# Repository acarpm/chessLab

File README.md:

# ChessLab — Documentation technique

Échiquier connecté détectant la position des pièces (capteurs à effet Hall) et affichant un retour visuel case par case (LEDs RGB adressables), pour visualiser une partie et aider à l'apprentissage du jeu.

## Architecture système

```
                        ESP32-C6
        WiFi 6 · BLE 5 · RISC-V 160 MHz · 512 KB SRAM
                            |
        +-------------------+-------------------+
        |                   |                   |
  Capteurs Hall         LEDs RGB           Alimentation
   (8x8 = 64)          (8x8 = 64)          Pack 18650
```

## Hardware

### Capteurs de position — SS49E

Capteur à effet Hall Analogique, suffisant pour détecter la présence ou l'absence d'une pièce sur une case. 

### LEDs — WS2812B (NeoPixel)

64 LEDs adressables individuellement, câblées en une seule chaîne série (une ligne de données, montage serpentin case par case). Alimentation 5 V, consommation crête d'environ 60 mA par LED.

### Multiplexage des capteurs Hall

64 capteurs analogiques dépassent le nombre de broches disponibles sur l'ESP32-C6. Solution retenue : multiplexeurs analogiques 74HC4051 (8 voies vers 1), soit 8 multiplexeurs pour 64 capteurs, ramenant le besoin à environ 11 broches ESP32.

### Alimentation — 18650

- 2 cellules 18650 montées en parallèle (~6000 mAh)
- Gestion de charge : IC TP4056
- Régulation :
  - 5 V / 3 A pour les LEDs WS2812B (convertisseur buck MP3608)
  - 3,3 V pour l'ESP32 et les capteurs Hall (LDO AMS1117-3.3)

## Circuit d'alimentation (mise sous tension)

Commutation assurée par un MOSFET P-Channel AO3401, piloté par le bouton d'alimentation et maintenu par l'ESP32 :

```
VBAT
 |
 R1 10k
 |
 +----------------------> Gate AO3401 (P-MOS)
 |                              |
 |        +---- R2 100k --------+
 |        |
 |     Source AO3401 = VBAT
 |        |
 |       Drain --------------------> VSYS
 |                                     |
BTN_PWR                          (MT3608 + AMS1117)
 |                                     |
 +---- vers Gate                 ESP32-C6
                                   |         |
                          GPIO_PWR_HOLD  GPIO_BTN_PWR
                          (maintien ON)  (lecture bouton)
```

**Séquence d'allumage**
1. Appui sur BTN_PWR
2. La gate du MOSFET passe à GND, le MOSFET conduit
3. VSYS s'active, l'ESP32 démarre
4. L'ESP32 maintient son GPIO à l'état bas pour garder le MOSFET conducteur
5. Le bouton peut être relâché, le système reste alimenté

**Extinction logicielle**
1. Inactivité détectée (par exemple 10 minutes sans coup joué)
2. Sauvegarde de l'état de la partie si nécessaire
3. Le GPIO passe à l'état haut, le MOSFET se bloque et coupe l'alimentation

**Extinction manuelle**
1. Appui long sur BTN_PWR (environ 3 secondes)
2. Détection par l'ESP32 via le GPIO de lecture du bouton
3. Même séquence que l'extinction logicielle

## Répartition des composants entre les deux cartes

| Carte principale | Carte d'alimentation |
|---|---|
| ESP32-C6 | TP4056 |
| Connecteur USB-C | DW01A + FS8205A |
| 64× WS2812B | Connecteur 18650 |
| 64× SS49E | MT3608 (5 V) |
| 8× 74HC4051 | AMS1117 (3,3 V) |
| 1× 74HC138 | Commutation MOSFET |
| BTN_BOOT + BTN_RESET | BTN_PWR + LED power |
| Connecteur JST vers carte d'alimentation | Connecteur JST vers carte principale |

Les deux cartes sont reliées par un connecteur JST 4 broches :

| Broche | Signal |
|---|---|
| 1 | VBAT (18650+) |
| 2 | GND |
| 3 | 5 V (sortie MT3608 vers carte principale) |
| 4 | 3,3 V (sortie AMS1117 vers carte principale) |

## Layout PCB

- Routage serpentin des WS2812B (entrée/sortie de données case par case)
- Matrices de capteurs Hall organisées en lignes/colonnes vers les multiplexeurs
- Épaisseur de PCB standard : 1,6 mm
- Couche diffusante imprimée en 3D au-dessus des LEDs

### Largeurs de piste

| Signal | Largeur |
|---|---|
| Données / GPIO | 0,25 mm |
| Alimentation 3,3 V | 0,5 mm |
| Alimentation 5 V (LEDs) | 1,0 mm |
| VBAT | 1,0 mm |
| VSYS | 1,0 mm |
| USB D+ / D- | 0,2 mm |

### Vias

| Type | Perçage | Pad |
|---|---|---|
| Standard | 0,4 mm | 0,8 mm |
| Puissance | 0,6 mm | 1,2 mm |

## Pinout ESP32-C6

| Broche | GPIO | Fonction |
|---|---|---|
| 13 | GPIO12 | USB D- |
| 14 | GPIO13 | USB D+ |
| 8 | GPIO0 | Mux — sélection canal S0 |
| 9 | GPIO1 | Mux — sélection canal S1 |
| 27 | GPIO2 | Mux — sélection canal S2 |
| 16 | GPIO18 | 74HC138 — sélection rangée A0 |
| 25 | GPIO16 | 74HC138 — sélection rangée A1 |
| 24 | GPIO17 | 74HC138 — sélection rangée A2 |
| 26 | GPIO3 | Lecture capteurs Hall (A_OUT) |
| 17 | GPIO19 | Données WS2812B (via résistance 33 Ω) |
| 18 | GPIO20 | VBAT |
| 15 | GPIO9 | Bouton BOOT |
| 19 | GPIO21 | Lecture bouton d'alimentation (BTN_PWR) |
| 20 | GPIO22 | Maintien alimentation (PWR_HOLD) |

## Fixation des pièces

Aimants cylindriques N52, Ø6×3 mm, insérés dans la base de chaque pièce et collés à l'époxy dans un logement imprimé en 3D. Ce choix permet une détection fiable par les capteurs Hall tout en restant invisible une fois la pièce posée.

## Boîtier

Hauteur totale estimée : 25 à 30 mm, dimensionnée pour loger la carte principale, la carte d'alimentation et les deux packs 18650.

## Firmware

Architecture logicielle sous FreeRTOS, organisée en tâches indépendantes :

| Tâche | Rôle |
|---|---|
| Hall Scanner | Scrutation des 64 capteurs (polling 50 ms) |
| LED Controller | Traduction de l'état de l'échiquier en animation LED |
| Chess Engine | Validation des positions et des coups légaux |
| BLE/WiFi | Communication avec l'application mobile ou l'interface web |
| Battery Monitor | Suivi de la tension batterie via diviseur de tension sur ADC |

**Bibliothèques envisagées**
- `FastLED` ou `Adafruit NeoPixel` pour le pilotage des WS2812B
- `Stockfish` (version allégée, via WASM) pour le moteur d'échecs
- Interface web servie depuis la mémoire flash (SPIFFS/LittleFS)

## Feuille de route

| Phase | Objectif |
|---|---|
| P1 | Prototype d'une case (1 LED + 1 capteur Hall + multiplexeur) sur breadboard |
| P2 | PCB de test 4×4 (KiCad) pour valider le multiplexage |
| P3 | PCB complet 8×8 et boîtier v1 |
| P4 | Firmware — moteur d'échecs et application |
| P5 | Impression 3D du boîtier final et des pièces modifiées |

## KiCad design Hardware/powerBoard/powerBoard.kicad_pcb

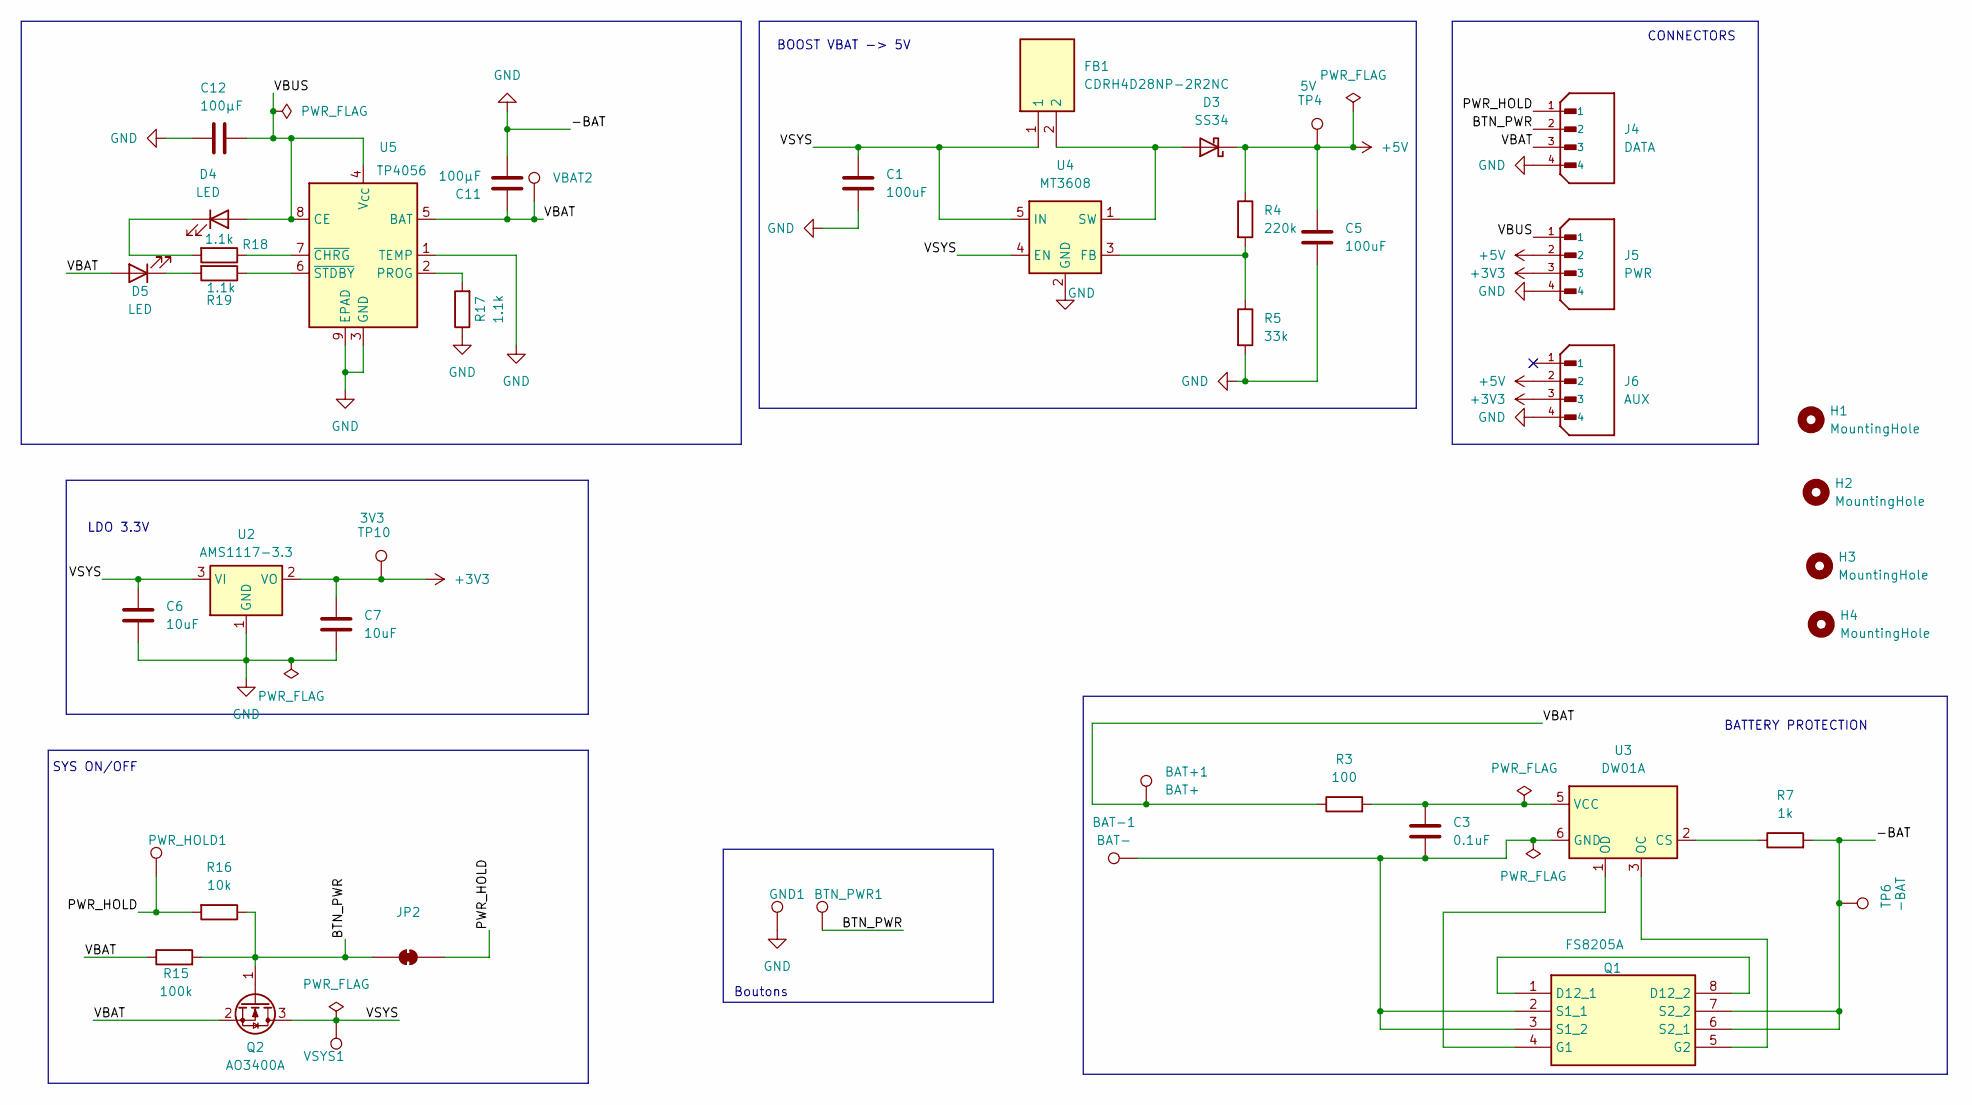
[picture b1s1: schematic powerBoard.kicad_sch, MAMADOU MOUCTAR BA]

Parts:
BAT+1: BAT+; TestPoint_Pad_4.0x4.0mm
BAT-1: BAT-; TestPoint_Pad_4.0x4.0mm
BTN_PWR1: TestPoint_Pad_4.0x4.0mm
C1, C5: 100uF; C_1206_3216Metric_Pad1.33x1.80mm_HandSolder
C3: 0.1uF; C_0603_1608Metric_Pad1.08x0.95mm_HandSolder
C6, C7: 10uF; C_0603_1608Metric_Pad1.08x0.95mm_HandSolder
C11, C12: 100µF; C_0603_1608Metric_Pad1.08x0.95mm_HandSolder
D3: SS34; D_SMA
D4, D5: LED; LED_0201_0603Metric
FB1: CDRH4D28NP-2R2NC; CDRH4D28NP100NC; Mouser Part Number 851-CDRH4D28NP-2R2NC
GND1: TestPoint_Pad_4.0x4.0mm
H1, H2, H3, H4: MountingHole; MountingHole_2.7mm_M2.5
J4: DATA; JST_B4B-XH-A_LF__SN_; PARTREV 7/4/21
J5: PWR; JST_B4B-XH-A_LF__SN_; PARTREV 7/4/21
J6: AUX; JST_B4B-XH-A_LF__SN_; PARTREV 7/4/21
JP2: SolderJumper_2_Bridged; SolderJumper-2_P1.3mm_Bridged2Bar_RoundedPad1.0x1.5mm
PWR_HOLD1: TestPoint_Pad_4.0x4.0mm
Q1: FS8205A; SOP65P640X120-8N; Manufacturer_Part_Number FS8205A
Q2: AO3400A; SOT-23
R3: 100; R_0603_1608Metric_Pad0.98x0.95mm_HandSolder
R4: 220k; R_0603_1608Metric_Pad0.98x0.95mm_HandSolder
R5: 33k; R_0603_1608Metric_Pad0.98x0.95mm_HandSolder
R7: 1k; R_0603_1608Metric_Pad0.98x0.95mm_HandSolder
R15: 100k; R_0603_1608Metric_Pad0.98x0.95mm_HandSolder
R16: 10k; R_0603_1608Metric_Pad0.98x0.95mm_HandSolder
R17, R18, R19: 1.1k; R_0603_1608Metric_Pad0.98x0.95mm_HandSolder
TP4: 5V; TestPoint_Pad_D2.0mm
TP6: -BAT; TestPoint_Pad_D2.0mm
TP10: 3V3; TestPoint_Pad_D2.0mm
U2: AMS1117-3.3; SOT-223-3_TabPin2
U3: DW01A; SOT-23-6
U4: MT3608; SOT-23-6
U5: TP4056; SOIC-8-1EP_3.9x4.9mm_P1.27mm_EP2.41x3.3mm_ThermalVias
VBAT2: TestPoint_Pad_4.0x4.0mm
VSYS1: TestPoint_Pad_4.0x4.0mm

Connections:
+3V3: C7.1, J5.3, J6.3, TP10.1 (1_1), U2.2 (VO)
+5V: C5.1, D3.1 (K), J5.2, J6.2, R4.1, TP4.1 (1_1)
/BTN_PWR: BTN_PWR1.1 (1_1), J4.2, JP2.1 (A), Q2.1 (G), R15.2, R16.1
/PWR_HOLD: J4.1, JP2.2 (B), PWR_HOLD1.1 (1_1), R16.2
/VBAT: BAT+1.1 (1_1), C11.1, D5.2 (A), J4.3, Q2.2 (S), R3.1, R15.1, U5.5 (BAT), VBAT2.1 (1_1)
/VBUS: C12.1, D4.2 (A), J5.1, U5.4 (V_{CC}), U5.8 (CE)
/VSYS: C1.1, C6.1, FB1.1, Q2.3 (D), U2.3 (VI), U4.4 (EN), U4.5 (IN), VSYS1.1 (1_1)
GND: C1.2, C5.2, C6.2, C7.2, C11.2, C12.2, GND1.1 (1_1), J4.4, J5.4, J6.4, Q1.6 (S2_1), Q1.7 (S2_2), R5.2, R7.2, R17.1, TP6.1 (1_1), U2.1 (GND), U4.2 (GND), U5.1 (TEMP), U5.3 (GND), U5.9 (EPAD)
unnamed: D3.2 (A), FB1.2, U4.1 (SW)
unnamed: D4.1 (K), R18.2
unnamed: D5.1 (K), R19.2
unnamed: Q1.1 (D12_1), Q1.8 (D12_2)
unnamed: Q1.4 (G1), U3.1 (OD)
unnamed: Q1.5 (G2), U3.3 (OC)
unnamed: BAT-1.1 (1_1), C3.2, Q1.2 (S1_1), Q1.3 (S1_2), U3.6 (GND)
unnamed: R7.1, U3.2 (CS)
unnamed: C3.1, R3.2, U3.5 (VCC)
unnamed: R4.2, R5.1, U4.3 (FB)
unnamed: R17.2, U5.2 (PROG)
unnamed: R18.1, U5.7 (~CHRG)
unnamed: R19.1, U5.6 (~STDBY)

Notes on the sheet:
BOOST VBAT -> 5V
CONNECTORS
BATTERY PROTECTION
LDO 3.3V
SYS ON/OFF
Boutons

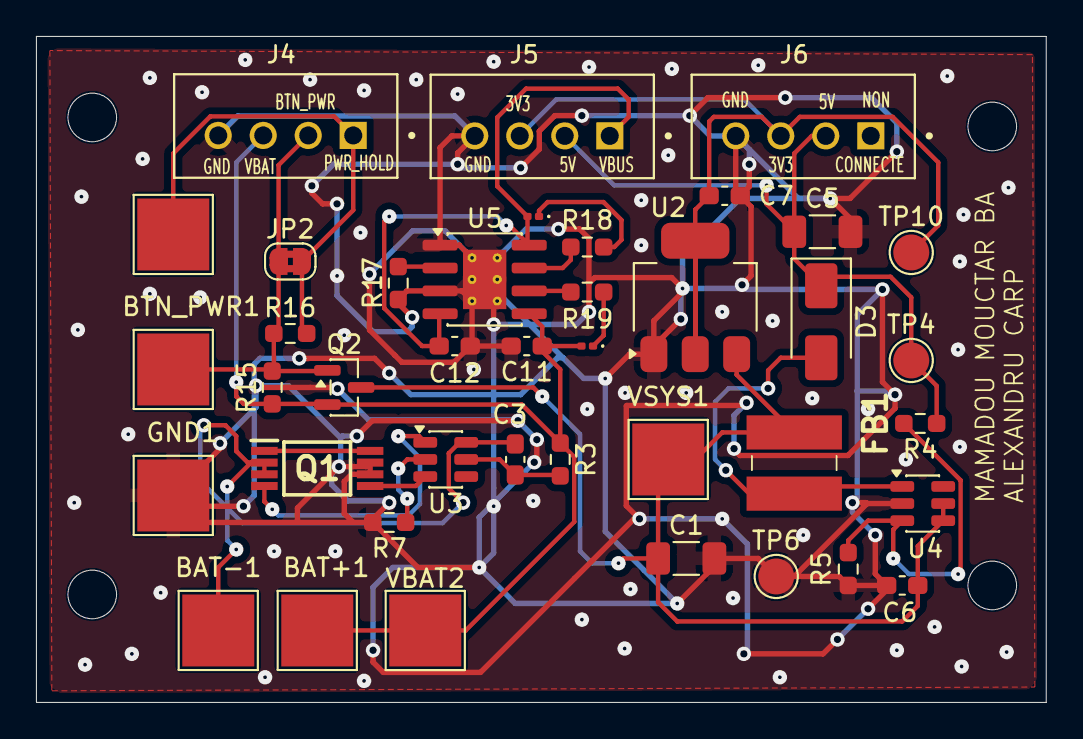
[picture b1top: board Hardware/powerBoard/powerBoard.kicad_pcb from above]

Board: 2 copper layers, 56.1 x 37.0 mm, 44 parts (0 on the bottom side), 21 nets.

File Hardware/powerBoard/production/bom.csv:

Designator,Footprint,Quantity,Value,LCSC Part #
BAT+1,TestPoint_Pad_4.0x4.0mm,1,BAT+,
BAT-1,TestPoint_Pad_4.0x4.0mm,1,BAT-,
"BTN_PWR1, GND1, PWR_HOLD1, VBAT2, VSYS1",TestPoint_Pad_4.0x4.0mm,5,~,
"C1, C5",1206,2,100uF,
"C11, C12",0603,2,100µF,
C3,0603,1,0.1uF,
"C6, C7",0603,2,10uF,
D3,D_SMA,1,SS34,
"D4, D5",0201,2,LED,
FB1,CDRH4D28NP100NC,1,CDRH4D28NP-2R2NC,
J4,JST_B4B-XH-A_LF__SN_,1,DATA,
J5,JST_B4B-XH-A_LF__SN_,1,PWR,
J6,JST_B4B-XH-A_LF__SN_,1,AUX,
Q1,SOP65P640X120-8N,1,FS8205A,
Q2,SOT-23,1,AO3400A,
R15,0603,1,100k,
R16,0603,1,10k,
"R17, R18, R19",0603,3,1.1k,
R3,0603,1,100,
R4,0603,1,220k,
R5,0603,1,33k,
R7,0603,1,1k,
TP10,TestPoint_Pad_D2.0mm,1,3V3,
TP4,TestPoint_Pad_D2.0mm,1,5V,
TP6,TestPoint_Pad_D2.0mm,1,-BAT,
U2,SOT-223-3_TabPin2,1,AMS1117-3.3,
U3,SOT-23-6,1,DW01A,
U4,SOT-23-6,1,MT3608,
U5,SOIC-8-1EP_3.9x4.9mm_P1.27mm_EP2.41x3.3mm_ThermalVias,1,TP4056,

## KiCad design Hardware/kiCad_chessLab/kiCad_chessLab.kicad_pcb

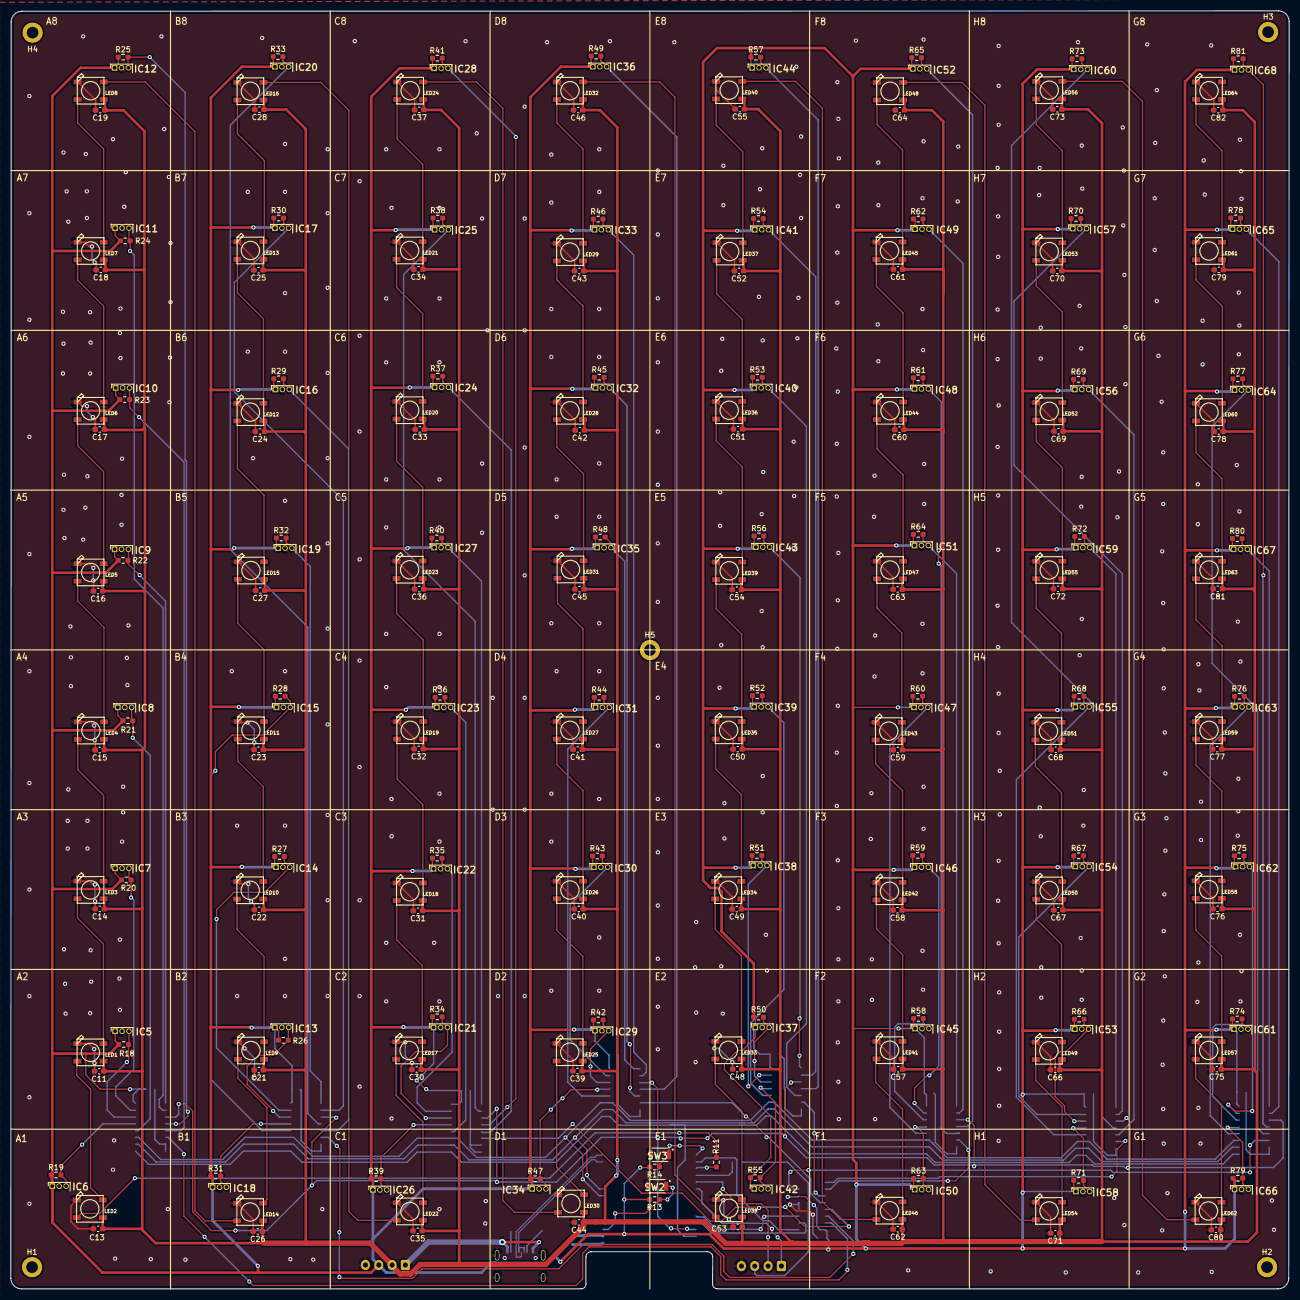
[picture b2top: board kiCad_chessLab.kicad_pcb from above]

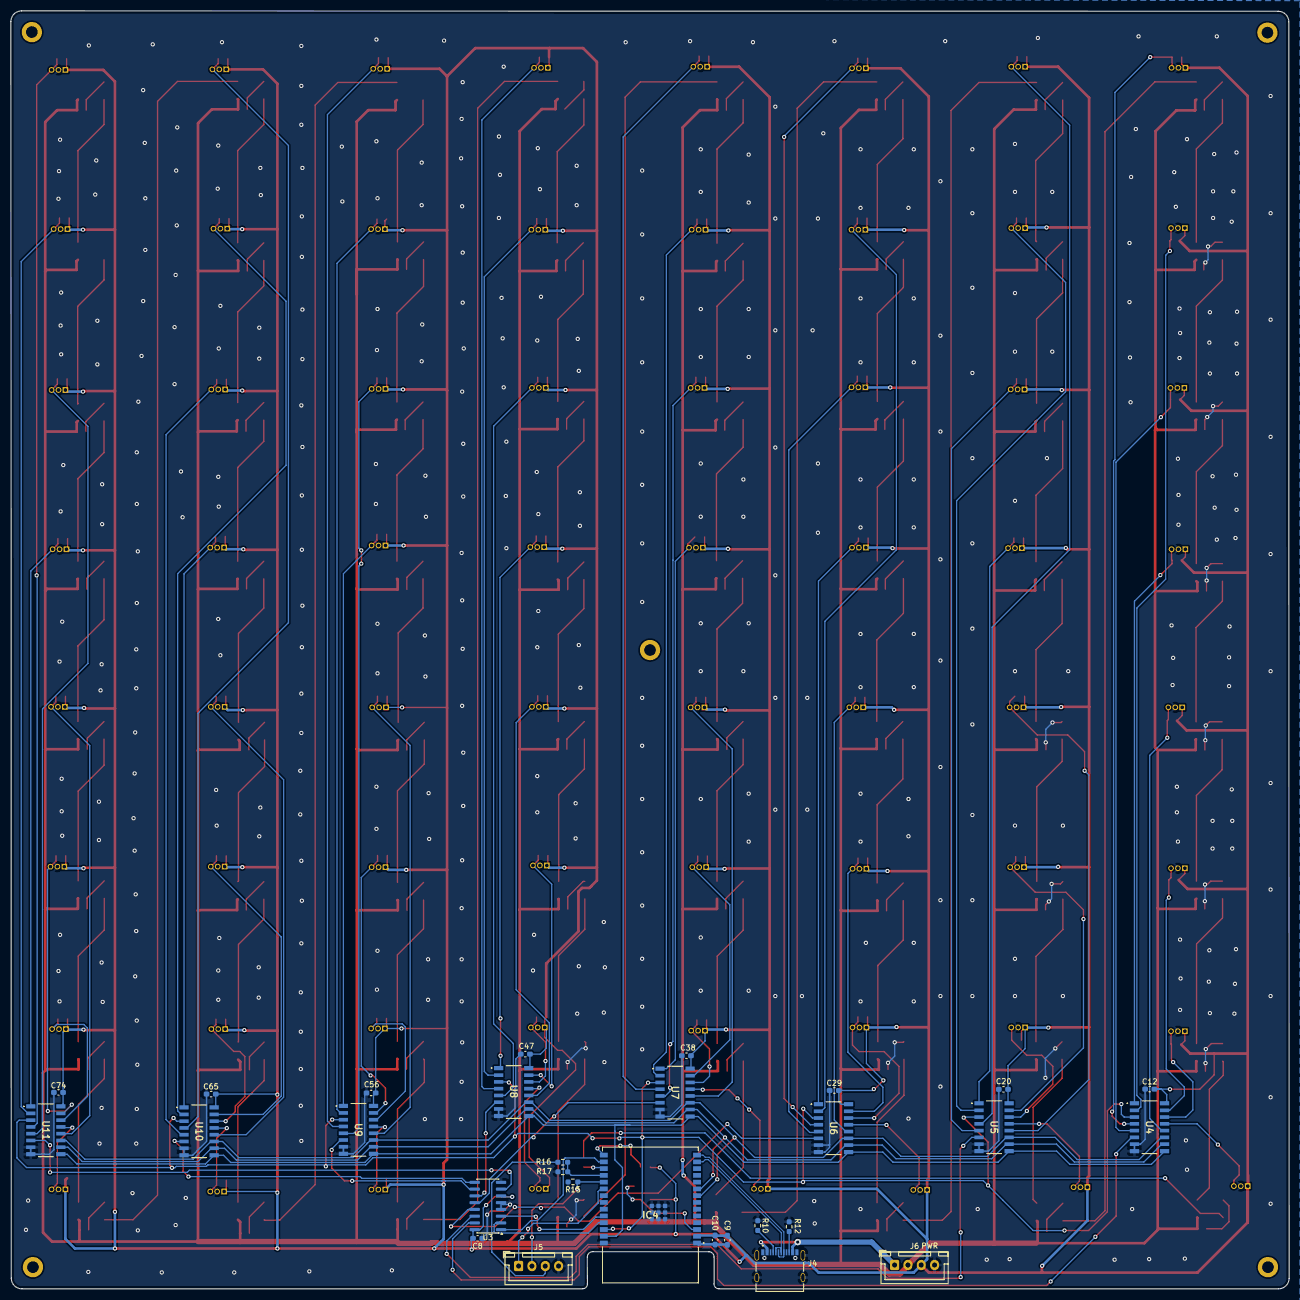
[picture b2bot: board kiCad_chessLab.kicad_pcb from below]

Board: 2 copper layers, 240.0 x 239.9 mm, 295 parts (29 on the bottom side), 158 nets.

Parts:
C8, C11, C12, C13, C14, C15, C16, C17, C18, C19, C20, C21, C22, C23, C24, C25, C26, C27, C28, C29, C30, C31, C32, C33, C34, C35, C36, C37, C38, C39, C40, C41, C42, C43, C44, C45, C46, C47, C48, C49, C50, C51, C52, C53, C54, C55, C56, C57, C58, C59, C60, C61, C62, C63, C64, C65, C66, C67, C68, C69, C70, C71, C72, C73, C74, C75, C76, C77, C78, C79, C80, C81, C82: 100nF; C_0603_1608Metric_Pad1.08x0.95mm_HandSolder
C9: 100uF; C_0603_1608Metric_Pad1.08x0.95mm_HandSolder
C10: 10uF; C_0603_1608Metric_Pad1.08x0.95mm_HandSolder
H1, H2, H3, H4, H5: MountingHole_Pad; MountingHole_2.2mm_M2_DIN965_Pad
IC4: ESP32-C6-WROOM-1-N8; ESP32C6WROOM1N8
IC5, IC6, IC7, IC8, IC9, IC10, IC11, IC12, IC13, IC14, IC15, IC16, IC17, IC18, IC19, IC20, IC21, IC22, IC23, IC24, IC25, IC26, IC27, IC28, IC29, IC30, IC31, IC32, IC33, IC34, IC35, IC36, IC37, IC38, IC39, IC40, IC41, IC42, IC43, IC44, IC45, IC46, IC47, IC48, IC49, IC50, IC51, IC52, IC53, IC54, IC55, IC56, IC57, IC58, IC59, IC60, IC61, IC62, IC63, IC64, IC65, IC66, IC67, IC68: SS49E; TO130P160X410X300-3P
J4: TYPE-C-31-M-12; HRO_TYPE-C-31-M-12
J5: DATA; JST_XH_B4B-XH-A_1x04_P2.50mm_Vertical
J6: PWR; JST_XH_B4B-XH-A_1x04_P2.50mm_Vertical
LED1, LED2, LED3, LED4, LED5, LED6, LED7, LED8, LED9, LED10, LED11, LED12, LED13, LED14, LED15, LED16, LED17, LED18, LED19, LED20, LED21, LED22, LED23, LED24, LED25, LED26, LED27, LED28, LED29, LED30, LED31, LED32, LED33, LED34, LED35, LED36, LED37, LED38, LED39, LED40, LED41, LED42, LED43, LED44, LED45, LED46, LED47, LED48, LED49, LED50, LED51, LED52, LED53, LED54, LED55, LED56, LED57, LED58, LED59, LED60, LED61, LED62, LED63, LED64: WS2812B
R10, R12: 5.1k; R_0603_1608Metric_Pad0.98x0.95mm_HandSolder
R11: 33; R_0603_1608Metric_Pad0.98x0.95mm_HandSolder
R13, R14, R15, R18, R19, R20, R21, R22, R23, R24, R25, R26, R27, R28, R29, R30, R31, R32, R33, R34, R35, R36, R37, R38, R39, R40, R41, R42, R43, R44, R45, R46, R47, R48, R49, R50, R51, R52, R53, R54, R55, R56, R57, R58, R59, R60, R61, R62, R63, R64, R65, R66, R67, R68, R69, R70, R71, R72, R73, R74, R75, R76, R77, R78, R79, R80, R81: 10k; R_0603_1608Metric_Pad0.98x0.95mm_HandSolder
R16, R17: 100k; R_0603_1608Metric_Pad0.98x0.95mm_HandSolder
SW2: RST; B3U-1000P
SW3: BOOT; B3U-1000P
U3: 74HC138; SOIC-16_3.9x9.9mm_P1.27mm
U4, U5, U6, U7, U8, U9, U10, U11: 74HC4051; 74HC4051D653

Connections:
+3V3: C8.2, C9.2, C10.2, C12.1, C20.1, C29.1, C38.1, C47.1, C56.1, C65.1, C74.1, IC4.2 (3V3), IC5.1 (+), IC6.1 (+), IC7.1 (+), IC8.1 (+), IC9.1 (+), IC10.1 (+), IC11.1 (+), IC12.1 (+), IC13.1 (+), IC14.1 (+), IC15.1 (+), IC16.1 (+), IC17.1 (+), IC18.1 (+), IC19.1 (+), IC20.1 (+), IC21.1 (+), IC22.1 (+), IC23.1 (+), IC24.1 (+), IC25.1 (+), IC26.1 (+), IC27.1 (+), IC28.1 (+), IC29.1 (+), IC30.1 (+), IC31.1 (+), IC32.1 (+), IC33.1 (+), IC34.1 (+), IC35.1 (+), IC36.1 (+), IC37.1 (+), IC38.1 (+), IC39.1 (+), IC40.1 (+), IC41.1 (+), IC42.1 (+), IC43.1 (+), IC44.1 (+), IC45.1 (+), IC46.1 (+), IC47.1 (+), IC48.1 (+), IC49.1 (+), IC50.1 (+), IC51.1 (+), IC52.1 (+), IC53.1 (+), IC54.1 (+), IC55.1 (+), IC56.1 (+), IC57.1 (+), IC58.1 (+), IC59.1 (+), IC60.1 (+), IC61.1 (+), IC62.1 (+), IC63.1 (+), IC64.1 (+), IC65.1 (+), IC66.1 (+), IC67.1 (+), IC68.1 (+), J6.3, R13.2, R14.2, R18.1, R19.1, R20.1, R21.1, R22.1, R23.1, R24.1, R25.1, R26.1, R27.1, R28.1, R29.1, R30.1, R31.1, R32.1, R33.1, R34.1, R35.1, R36.1, R37.1, R38.1, R39.1, R40.1, R41.1, R42.1, R43.1, R44.1, R45.1, R46.1, R47.1, R48.1, R49.1, R50.1, R51.1, R52.1, R53.1, R54.1, R55.1, R56.1, R57.1, R58.1, R59.1, R60.1, R61.1, R62.1, R63.1, R64.1, R65.1, R66.1, R67.1, R68.1, R69.1, R70.1, R71.1, R72.1, R73.1, R74.1, R75.1, R76.1, R77.1, R78.1, R79.1, R80.1, R81.1, U3.6 (E2), U3.16 (VCC), U4.16 (VCC), U5.16 (VCC), U6.16 (VCC), U7.16 (VCC), U8.16 (VCC), U9.16 (VCC), U10.16 (VCC), U11.16 (VCC)
+5V: C11.1, C13.1, C14.1, C15.1, C16.1, C17.1, C18.1, C19.1, C21.1, C22.1, C23.1, C24.1, C25.1, C26.1, C27.1, C28.1, C30.1, C31.1, C32.1, C33.1, C34.1, C35.1, C36.1, C37.1, C39.1, C40.1, C41.1, C42.1, C43.1, C44.1, C45.1, C46.1, C48.1, C49.1, C50.1, C51.1, C52.1, C53.1, C54.1, C55.1, C57.1, C58.1, C59.1, C60.1, C61.1, C62.1, C63.1, C64.1, C66.1, C67.1, C68.1, C69.1, C70.1, C71.1, C72.1, C73.1, C75.1, C76.1, C77.1, C78.1, C79.1, C80.1, C81.1, C82.1, J6.2, LED1.1-VDD (VDD), LED2.1-VDD (VDD), LED3.1-VDD (VDD), LED4.1-VDD (VDD), LED5.1-VDD (VDD), LED6.1-VDD (VDD), LED7.1-VDD (VDD), LED8.1-VDD (VDD), LED9.1-VDD (VDD), LED10.1-VDD (VDD), LED11.1-VDD (VDD), LED12.1-VDD (VDD), LED13.1-VDD (VDD), LED14.1-VDD (VDD), LED15.1-VDD (VDD), LED16.1-VDD (VDD), LED17.1-VDD (VDD), LED18.1-VDD (VDD), LED19.1-VDD (VDD), LED20.1-VDD (VDD), LED21.1-VDD (VDD), LED22.1-VDD (VDD), LED23.1-VDD (VDD), LED24.1-VDD (VDD), LED25.1-VDD (VDD), LED26.1-VDD (VDD), LED27.1-VDD (VDD), LED28.1-VDD (VDD), LED29.1-VDD (VDD), LED30.1-VDD (VDD), LED31.1-VDD (VDD), LED32.1-VDD (VDD), LED33.1-VDD (VDD), LED34.1-VDD (VDD), LED35.1-VDD (VDD), LED36.1-VDD (VDD), LED37.1-VDD (VDD), LED38.1-VDD (VDD), LED39.1-VDD (VDD), LED40.1-VDD (VDD), LED41.1-VDD (VDD), LED42.1-VDD (VDD), LED43.1-VDD (VDD), LED44.1-VDD (VDD), LED45.1-VDD (VDD), LED46.1-VDD (VDD), LED47.1-VDD (VDD), LED48.1-VDD (VDD), LED49.1-VDD (VDD), LED50.1-VDD (VDD), LED51.1-VDD (VDD), LED52.1-VDD (VDD), LED53.1-VDD (VDD), LED54.1-VDD (VDD), LED55.1-VDD (VDD), LED56.1-VDD (VDD), LED57.1-VDD (VDD), LED58.1-VDD (VDD), LED59.1-VDD (VDD), LED60.1-VDD (VDD), LED61.1-VDD (VDD), LED62.1-VDD (VDD), LED63.1-VDD (VDD), LED64.1-VDD (VDD)
/Main Board/A0: IC4.16 (IO18), U3.1 (A0)
/Main Board/A1: IC4.21 (IO23), IC4.25 (TXD0), U3.2 (A1)
/Main Board/A2: IC4.24 (RXD0), U3.3 (A2)
/Main Board/A_OUT: IC4.26 (IO3), U4.3 (A), U5.3 (A), U6.3 (A), U7.3 (A), U8.3 (A), U9.3 (A), U10.3 (A), U11.3 (A)
/Main Board/BTN_PWR: IC4.19 (IO21), J5.2, R15.1
/Main Board/DIN: IC4.17 (IO19), R11.1
/Main Board/DN: IC4.13 (IO12), J4.A7 (DN1), J4.B7 (DN2)
/Main Board/DP: IC4.14 (IO13), J4.A6 (DP1), J4.B6 (DP2)
/Main Board/PWR_HOLD: IC4.20 (IO22), J5.1
/Main Board/Row_A/DIN: LED2.4-DIN (DI), R11.2
/Main Board/Row_A/DOUT: LED8.2-DOUT (DO), LED14.4-DIN (DI)
/Main Board/Row_A/En: U3.15 (~Y0), U4.6 (~E)
/Main Board/Row_A/cell_B1/DOUT: LED1.4-DIN (DI), LED2.2-DOUT (DO)
/Main Board/Row_A/cell_B1/SIG: IC6.3 (O), R19.2, U4.13 (A0)
/Main Board/Row_A/cell_B2/DOUT: LED1.2-DOUT (DO), LED3.4-DIN (DI)
/Main Board/Row_A/cell_B2/SIG: IC5.3 (O), R18.2, U4.14 (A1)
/Main Board/Row_A/cell_B3/DOUT: LED3.2-DOUT (DO), LED4.4-DIN (DI)
/Main Board/Row_A/cell_B3/SIG: IC7.3 (O), R20.2, U4.15 (A2)
/Main Board/Row_A/cell_B4/DOUT: LED4.2-DOUT (DO), LED5.4-DIN (DI)
/Main Board/Row_A/cell_B4/SIG: IC8.3 (O), R21.2, U4.12 (A3)
/Main Board/Row_A/cell_B5/DOUT: LED5.2-DOUT (DO), LED6.4-DIN (DI)
/Main Board/Row_A/cell_B5/SIG: IC9.3 (O), R22.2, U4.1 (A4)
/Main Board/Row_A/cell_B6/DOUT: LED6.2-DOUT (DO), LED7.4-DIN (DI)
/Main Board/Row_A/cell_B6/SIG: IC10.3 (O), R23.2, U4.5 (A5)
/Main Board/Row_A/cell_B7/DOUT: LED7.2-DOUT (DO), LED8.4-DIN (DI)
/Main Board/Row_A/cell_B7/SIG: IC11.3 (O), R24.2, U4.2 (A6)
/Main Board/Row_A/cell_B8/SIG: IC12.3 (O), R25.2, U4.4 (A7)
/Main Board/Row_B/DOUT: LED16.2-DOUT (DO), LED22.4-DIN (DI)
/Main Board/Row_B/En: U3.14 (~Y1), U5.6 (~E)
/Main Board/Row_B/cell_B1/DOUT: LED9.4-DIN (DI), LED14.2-DOUT (DO)
/Main Board/Row_B/cell_B1/SIG: IC18.3 (O), R31.2, U5.13 (A0)
/Main Board/Row_B/cell_B2/DOUT: LED9.2-DOUT (DO), LED10.4-DIN (DI)
/Main Board/Row_B/cell_B2/SIG: IC13.3 (O), R26.2, U5.14 (A1)
/Main Board/Row_B/cell_B3/DOUT: LED10.2-DOUT (DO), LED11.4-DIN (DI)
/Main Board/Row_B/cell_B3/SIG: IC14.3 (O), R27.2, U5.15 (A2)
/Main Board/Row_B/cell_B4/DOUT: LED11.2-DOUT (DO), LED15.4-DIN (DI)
/Main Board/Row_B/cell_B4/SIG: IC15.3 (O), R28.2, U5.12 (A3)
/Main Board/Row_B/cell_B5/DOUT: LED12.4-DIN (DI), LED15.2-DOUT (DO)
/Main Board/Row_B/cell_B5/SIG: IC19.3 (O), R32.2, U5.1 (A4)
/Main Board/Row_B/cell_B6/DOUT: LED12.2-DOUT (DO), LED13.4-DIN (DI)
/Main Board/Row_B/cell_B6/SIG: IC16.3 (O), R29.2, U5.5 (A5)
/Main Board/Row_B/cell_B7/DOUT: LED13.2-DOUT (DO), LED16.4-DIN (DI)
/Main Board/Row_B/cell_B7/SIG: IC17.3 (O), R30.2, U5.2 (A6)
/Main Board/Row_B/cell_B8/SIG: IC20.3 (O), R33.2, U5.4 (A7)
/Main Board/Row_C/DOUT: LED24.2-DOUT (DO), LED30.4-DIN (DI)
/Main Board/Row_C/En: U3.13 (~Y2), U6.6 (~E)
/Main Board/Row_C/cell_B1/DOUT: LED17.4-DIN (DI), LED22.2-DOUT (DO)
/Main Board/Row_C/cell_B1/SIG: IC26.3 (O), R39.2, U6.13 (A0)
/Main Board/Row_C/cell_B2/DOUT: LED17.2-DOUT (DO), LED18.4-DIN (DI)
/Main Board/Row_C/cell_B2/SIG: IC21.3 (O), R34.2, U6.14 (A1)
/Main Board/Row_C/cell_B3/DOUT: LED18.2-DOUT (DO), LED19.4-DIN (DI)
/Main Board/Row_C/cell_B3/SIG: IC22.3 (O), R35.2, U6.15 (A2)
/Main Board/Row_C/cell_B4/DOUT: LED19.2-DOUT (DO), LED23.4-DIN (DI)
/Main Board/Row_C/cell_B4/SIG: IC23.3 (O), R36.2, U6.12 (A3)
/Main Board/Row_C/cell_B5/DOUT: LED20.4-DIN (DI), LED23.2-DOUT (DO)
/Main Board/Row_C/cell_B5/SIG: IC27.3 (O), R40.2, U6.1 (A4)
/Main Board/Row_C/cell_B6/DOUT: LED20.2-DOUT (DO), LED21.4-DIN (DI)
/Main Board/Row_C/cell_B6/SIG: IC24.3 (O), R37.2, U6.5 (A5)
/Main Board/Row_C/cell_B7/DOUT: LED21.2-DOUT (DO), LED24.4-DIN (DI)
/Main Board/Row_C/cell_B7/SIG: IC25.3 (O), R38.2, U6.2 (A6)
/Main Board/Row_C/cell_B8/SIG: IC28.3 (O), R41.2, U6.4 (A7)
/Main Board/Row_D/DOUT: LED32.2-DOUT (DO), LED38.4-DIN (DI)
/Main Board/Row_D/En: U3.12 (~Y3), U7.6 (~E)
/Main Board/Row_D/cell_B1/DOUT: LED25.4-DIN (DI), LED30.2-DOUT (DO)
/Main Board/Row_D/cell_B1/SIG: IC34.3 (O), R47.2, U7.13 (A0)
/Main Board/Row_D/cell_B2/DOUT: LED25.2-DOUT (DO), LED26.4-DIN (DI)
/Main Board/Row_D/cell_B2/SIG: IC29.3 (O), R42.2, U7.14 (A1)
/Main Board/Row_D/cell_B3/DOUT: LED26.2-DOUT (DO), LED27.4-DIN (DI)
/Main Board/Row_D/cell_B3/SIG: IC30.3 (O), R43.2, U7.15 (A2)
/Main Board/Row_D/cell_B4/DOUT: LED27.2-DOUT (DO), LED31.4-DIN (DI)
/Main Board/Row_D/cell_B4/SIG: IC31.3 (O), R44.2, U7.12 (A3)
/Main Board/Row_D/cell_B5/DOUT: LED28.4-DIN (DI), LED31.2-DOUT (DO)
/Main Board/Row_D/cell_B5/SIG: IC35.3 (O), R48.2, U7.1 (A4)
/Main Board/Row_D/cell_B6/DOUT: LED28.2-DOUT (DO), LED29.4-DIN (DI)
/Main Board/Row_D/cell_B6/SIG: IC32.3 (O), R45.2, U7.5 (A5)
/Main Board/Row_D/cell_B7/DOUT: LED29.2-DOUT (DO), LED32.4-DIN (DI)
/Main Board/Row_D/cell_B7/SIG: IC33.3 (O), R46.2, U7.2 (A6)
/Main Board/Row_D/cell_B8/SIG: IC36.3 (O), R49.2, U7.4 (A7)
/Main Board/Row_E/DOUT: LED40.2-DOUT (DO), LED46.4-DIN (DI)
/Main Board/Row_E/En: U3.11 (~Y4), U8.6 (~E)
/Main Board/Row_E/cell_B1/DOUT: LED33.4-DIN (DI), LED38.2-DOUT (DO)
/Main Board/Row_E/cell_B1/SIG: IC42.3 (O), R55.2, U8.13 (A0)
/Main Board/Row_E/cell_B2/DOUT: LED33.2-DOUT (DO), LED34.4-DIN (DI)
/Main Board/Row_E/cell_B2/SIG: IC37.3 (O), R50.2, U8.14 (A1)
/Main Board/Row_E/cell_B3/DOUT: LED34.2-DOUT (DO), LED35.4-DIN (DI)
/Main Board/Row_E/cell_B3/SIG: IC38.3 (O), R51.2, U8.15 (A2)
/Main Board/Row_E/cell_B4/DOUT: LED35.2-DOUT (DO), LED39.4-DIN (DI)
/Main Board/Row_E/cell_B4/SIG: IC39.3 (O), R52.2, U8.12 (A3)
/Main Board/Row_E/cell_B5/DOUT: LED36.4-DIN (DI), LED39.2-DOUT (DO)
/Main Board/Row_E/cell_B5/SIG: IC43.3 (O), R56.2, U8.1 (A4)
/Main Board/Row_E/cell_B6/DOUT: LED36.2-DOUT (DO), LED37.4-DIN (DI)
/Main Board/Row_E/cell_B6/SIG: IC40.3 (O), R53.2, U8.5 (A5)
/Main Board/Row_E/cell_B7/DOUT: LED37.2-DOUT (DO), LED40.4-DIN (DI)
/Main Board/Row_E/cell_B7/SIG: IC41.3 (O), R54.2, U8.2 (A6)
/Main Board/Row_E/cell_B8/SIG: IC44.3 (O), R57.2, U8.4 (A7)
/Main Board/Row_F/DOUT: LED48.2-DOUT (DO), LED54.4-DIN (DI)
/Main Board/Row_F/En: U3.10 (~Y5), U9.6 (~E)
/Main Board/Row_F/cell_B1/DOUT: LED41.4-DIN (DI), LED46.2-DOUT (DO)
/Main Board/Row_F/cell_B1/SIG: IC50.3 (O), R63.2, U9.13 (A0)
/Main Board/Row_F/cell_B2/DOUT: LED41.2-DOUT (DO), LED42.4-DIN (DI)
/Main Board/Row_F/cell_B2/SIG: IC45.3 (O), R58.2, U9.14 (A1)
/Main Board/Row_F/cell_B3/DOUT: LED42.2-DOUT (DO), LED43.4-DIN (DI)
/Main Board/Row_F/cell_B3/SIG: IC46.3 (O), R59.2, U9.15 (A2)
/Main Board/Row_F/cell_B4/DOUT: LED43.2-DOUT (DO), LED47.4-DIN (DI)
/Main Board/Row_F/cell_B4/SIG: IC47.3 (O), R60.2, U9.12 (A3)
/Main Board/Row_F/cell_B5/DOUT: LED44.4-DIN (DI), LED47.2-DOUT (DO)
/Main Board/Row_F/cell_B5/SIG: IC51.3 (O), R64.2, U9.1 (A4)
/Main Board/Row_F/cell_B6/DOUT: LED44.2-DOUT (DO), LED45.4-DIN (DI)
/Main Board/Row_F/cell_B6/SIG: IC48.3 (O), R61.2, U9.5 (A5)
/Main Board/Row_F/cell_B7/DOUT: LED45.2-DOUT (DO), LED48.4-DIN (DI)
/Main Board/Row_F/cell_B7/SIG: IC49.3 (O), R62.2, U9.2 (A6)
/Main Board/Row_F/cell_B8/SIG: IC52.3 (O), R65.2, U9.4 (A7)
/Main Board/Row_G/DOUT: LED56.2-DOUT (DO), LED62.4-DIN (DI)
/Main Board/Row_G/En: U3.9 (~Y6), U10.6 (~E)
/Main Board/Row_G/cell_B1/DOUT: LED49.4-DIN (DI), LED54.2-DOUT (DO)
/Main Board/Row_G/cell_B1/SIG: IC58.3 (O), R71.2, U10.13 (A0)
/Main Board/Row_G/cell_B2/DOUT: LED49.2-DOUT (DO), LED50.4-DIN (DI)
/Main Board/Row_G/cell_B2/SIG: IC53.3 (O), R66.2, U10.14 (A1)
/Main Board/Row_G/cell_B3/DOUT: LED50.2-DOUT (DO), LED51.4-DIN (DI)
/Main Board/Row_G/cell_B3/SIG: IC54.3 (O), R67.2, U10.15 (A2)
/Main Board/Row_G/cell_B4/DOUT: LED51.2-DOUT (DO), LED55.4-DIN (DI)
/Main Board/Row_G/cell_B4/SIG: IC55.3 (O), R68.2, U10.12 (A3)
/Main Board/Row_G/cell_B5/DOUT: LED52.4-DIN (DI), LED55.2-DOUT (DO)
/Main Board/Row_G/cell_B5/SIG: IC59.3 (O), R72.2, U10.1 (A4)
/Main Board/Row_G/cell_B6/DOUT: LED52.2-DOUT (DO), LED53.4-DIN (DI)
/Main Board/Row_G/cell_B6/SIG: IC56.3 (O), R69.2, U10.5 (A5)
/Main Board/Row_G/cell_B7/DOUT: LED53.2-DOUT (DO), LED56.4-DIN (DI)
/Main Board/Row_G/cell_B7/SIG: IC57.3 (O), R70.2, U10.2 (A6)
/Main Board/Row_G/cell_B8/SIG: IC60.3 (O), R73.2, U10.4 (A7)
/Main Board/Row_H/En: U3.7 (~Y7), U11.6 (~E)
/Main Board/Row_H/cell_B1/DOUT: LED57.4-DIN (DI), LED62.2-DOUT (DO)
/Main Board/Row_H/cell_B1/SIG: IC66.3 (O), R79.2, U11.13 (A0)
/Main Board/Row_H/cell_B2/DOUT: LED57.2-DOUT (DO), LED58.4-DIN (DI)
/Main Board/Row_H/cell_B2/SIG: IC61.3 (O), R74.2, U11.14 (A1)
/Main Board/Row_H/cell_B3/DOUT: LED58.2-DOUT (DO), LED59.4-DIN (DI)
/Main Board/Row_H/cell_B3/SIG: IC62.3 (O), R75.2, U11.15 (A2)
/Main Board/Row_H/cell_B4/DOUT: LED59.2-DOUT (DO), LED63.4-DIN (DI)
/Main Board/Row_H/cell_B4/SIG: IC63.3 (O), R76.2, U11.12 (A3)
/Main Board/Row_H/cell_B5/DOUT: LED60.4-DIN (DI), LED63.2-DOUT (DO)
/Main Board/Row_H/cell_B5/SIG: IC67.3 (O), R80.2, U11.1 (A4)
/Main Board/Row_H/cell_B6/DOUT: LED60.2-DOUT (DO), LED61.4-DIN (DI)
/Main Board/Row_H/cell_B6/SIG: IC64.3 (O), R77.2, U11.5 (A5)
/Main Board/Row_H/cell_B7/DOUT: LED61.2-DOUT (DO), LED64.4-DIN (DI)
/Main Board/Row_H/cell_B7/SIG: IC65.3 (O), R78.2, U11.2 (A6)
/Main Board/Row_H/cell_B8/SIG: IC68.3 (O), R81.2, U11.4 (A7)
/Main Board/S0: IC4.8 (IO0), U4.11 (S0), U5.11 (S0), U6.11 (S0), U7.11 (S0), U8.11 (S0), U9.11 (S0), U10.11 (S0), U11.11 (S0)
/Main Board/S1: IC4.9 (IO1), U4.10 (S1), U5.10 (S1), U6.10 (S1), U7.10 (S1), U8.10 (S1), U9.10 (S1), U10.10 (S1), U11.10 (S1)
/Main Board/S2: IC4.27 (IO2), U4.9 (S2), U5.9 (S2), U6.9 (S2), U7.9 (S2), U8.9 (S2), U9.9 (S2), U10.9 (S2), U11.9 (S2)
/Main Board/VBAT: J5.3, R16.2
GND: C8.1, C9.1, C10.1, C11.2, C12.2, C13.2, C14.2, C15.2, C16.2, C17.2, C18.2, C19.2, C20.2, C21.2, C22.2, C23.2, C24.2, C25.2, C26.2, C27.2, C28.2, C29.2, C30.2, C31.2, C32.2, C33.2, C34.2, C35.2, C36.2, C37.2, C38.2, C39.2, C40.2, C41.2, C42.2, C43.2, C44.2, C45.2, C46.2, C47.2, C48.2, C49.2, C50.2, C51.2, C52.2, C53.2, C54.2, C55.2, C56.2, C57.2, C58.2, C59.2, C60.2, C61.2, C62.2, C63.2, C64.2, C65.2, C66.2, C67.2, C68.2, C69.2, C70.2, C71.2, C72.2, C73.2, C74.2, C75.2, C76.2, C77.2, C78.2, C79.2, C80.2, C81.2, C82.2, IC4.1 (GND_1), IC4.28 (GND_2), IC4.29 (GND_3), IC4.30 (GND_4), IC4.31 (GND_5), IC4.32 (GND_6), IC4.33 (GND_7), IC4.34 (GND_8), IC4.35 (GND_9), IC4.36 (GND_10), IC4.37 (GND_11), IC5.2 (-), IC6.2 (-), IC7.2 (-), IC8.2 (-), IC9.2 (-), IC10.2 (-), IC11.2 (-), IC12.2 (-), IC13.2 (-), IC14.2 (-), IC15.2 (-), IC16.2 (-), IC17.2 (-), IC18.2 (-), IC19.2 (-), IC20.2 (-), IC21.2 (-), IC22.2 (-), IC23.2 (-), IC24.2 (-), IC25.2 (-), IC26.2 (-), IC27.2 (-), IC28.2 (-), IC29.2 (-), IC30.2 (-), IC31.2 (-), IC32.2 (-), IC33.2 (-), IC34.2 (-), IC35.2 (-), IC36.2 (-), IC37.2 (-), IC38.2 (-), IC39.2 (-), IC40.2 (-), IC41.2 (-), IC42.2 (-), IC43.2 (-), IC44.2 (-), IC45.2 (-), IC46.2 (-), IC47.2 (-), IC48.2 (-), IC49.2 (-), IC50.2 (-), IC51.2 (-), IC52.2 (-), IC53.2 (-), IC54.2 (-), IC55.2 (-), IC56.2 (-), IC57.2 (-), IC58.2 (-), IC59.2 (-), IC60.2 (-), IC61.2 (-), IC62.2 (-), IC63.2 (-), IC64.2 (-), IC65.2 (-), IC66.2 (-), IC67.2 (-), IC68.2 (-), J4.A1_B12 (GND), J4.B1_A12 (GND), J4.S1 (SHIELD), J4.S2 (SHIELD), J4.S3 (SHIELD), J4.S4 (SHIELD), J5.4, J6.4, LED1.3-GND (GND), LED2.3-GND (GND), LED3.3-GND (GND), LED4.3-GND (GND), LED5.3-GND (GND), LED6.3-GND (GND), LED7.3-GND (GND), LED8.3-GND (GND), LED9.3-GND (GND), LED10.3-GND (GND), LED11.3-GND (GND), LED12.3-GND (GND), LED13.3-GND (GND), LED14.3-GND (GND), LED15.3-GND (GND), LED16.3-GND (GND), LED17.3-GND (GND), LED18.3-GND (GND), LED19.3-GND (GND), LED20.3-GND (GND), LED21.3-GND (GND), LED22.3-GND (GND), LED23.3-GND (GND), LED24.3-GND (GND), LED25.3-GND (GND), LED26.3-GND (GND), LED27.3-GND (GND), LED28.3-GND (GND), LED29.3-GND (GND), LED30.3-GND (GND), LED31.3-GND (GND), LED32.3-GND (GND), LED33.3-GND (GND), LED34.3-GND (GND), LED35.3-GND (GND), LED36.3-GND (GND), LED37.3-GND (GND), LED38.3-GND (GND), LED39.3-GND (GND), LED40.3-GND (GND), LED41.3-GND (GND), LED42.3-GND (GND), LED43.3-GND (GND), LED44.3-GND (GND), LED45.3-GND (GND), LED46.3-GND (GND), LED47.3-GND (GND), LED48.3-GND (GND), LED49.3-GND (GND), LED50.3-GND (GND), LED51.3-GND (GND), LED52.3-GND (GND), LED53.3-GND (GND), LED54.3-GND (GND), LED55.3-GND (GND), LED56.3-GND (GND), LED57.3-GND (GND), LED58.3-GND (GND), LED59.3-GND (GND), LED60.3-GND (GND), LED61.3-GND (GND), LED62.3-GND (GND), LED63.3-GND (GND), LED64.3-GND (GND), R10.1, R12.2, R15.2, R17.1, SW2.2 (A), SW3.2 (A), U3.4 (~E0), U3.5 (~E1), U3.8 (GND), U4.7 (VEE), U4.8 (GND), U5.7 (VEE), U5.8 (GND), U6.7 (VEE), U6.8 (GND), U7.7 (VEE), U7.8 (GND), U8.7 (VEE), U8.8 (GND), U9.7 (VEE), U9.8 (GND), U10.7 (VEE), U10.8 (GND), U11.7 (VEE), U11.8 (GND)
unnamed: IC4.3 (EN), R13.1, SW2.1 (K)
unnamed: IC4.15 (IO9), R14.1, SW3.1 (K)
unnamed: IC4.18 (IO20), R16.1, R17.2
unnamed: J4.A5 (CC1), R10.2
unnamed: J4.B5 (CC2), R12.1
VBUS: J4.A4_B9 (VBUS), J4.B4_A9 (VBUS), J6.1
